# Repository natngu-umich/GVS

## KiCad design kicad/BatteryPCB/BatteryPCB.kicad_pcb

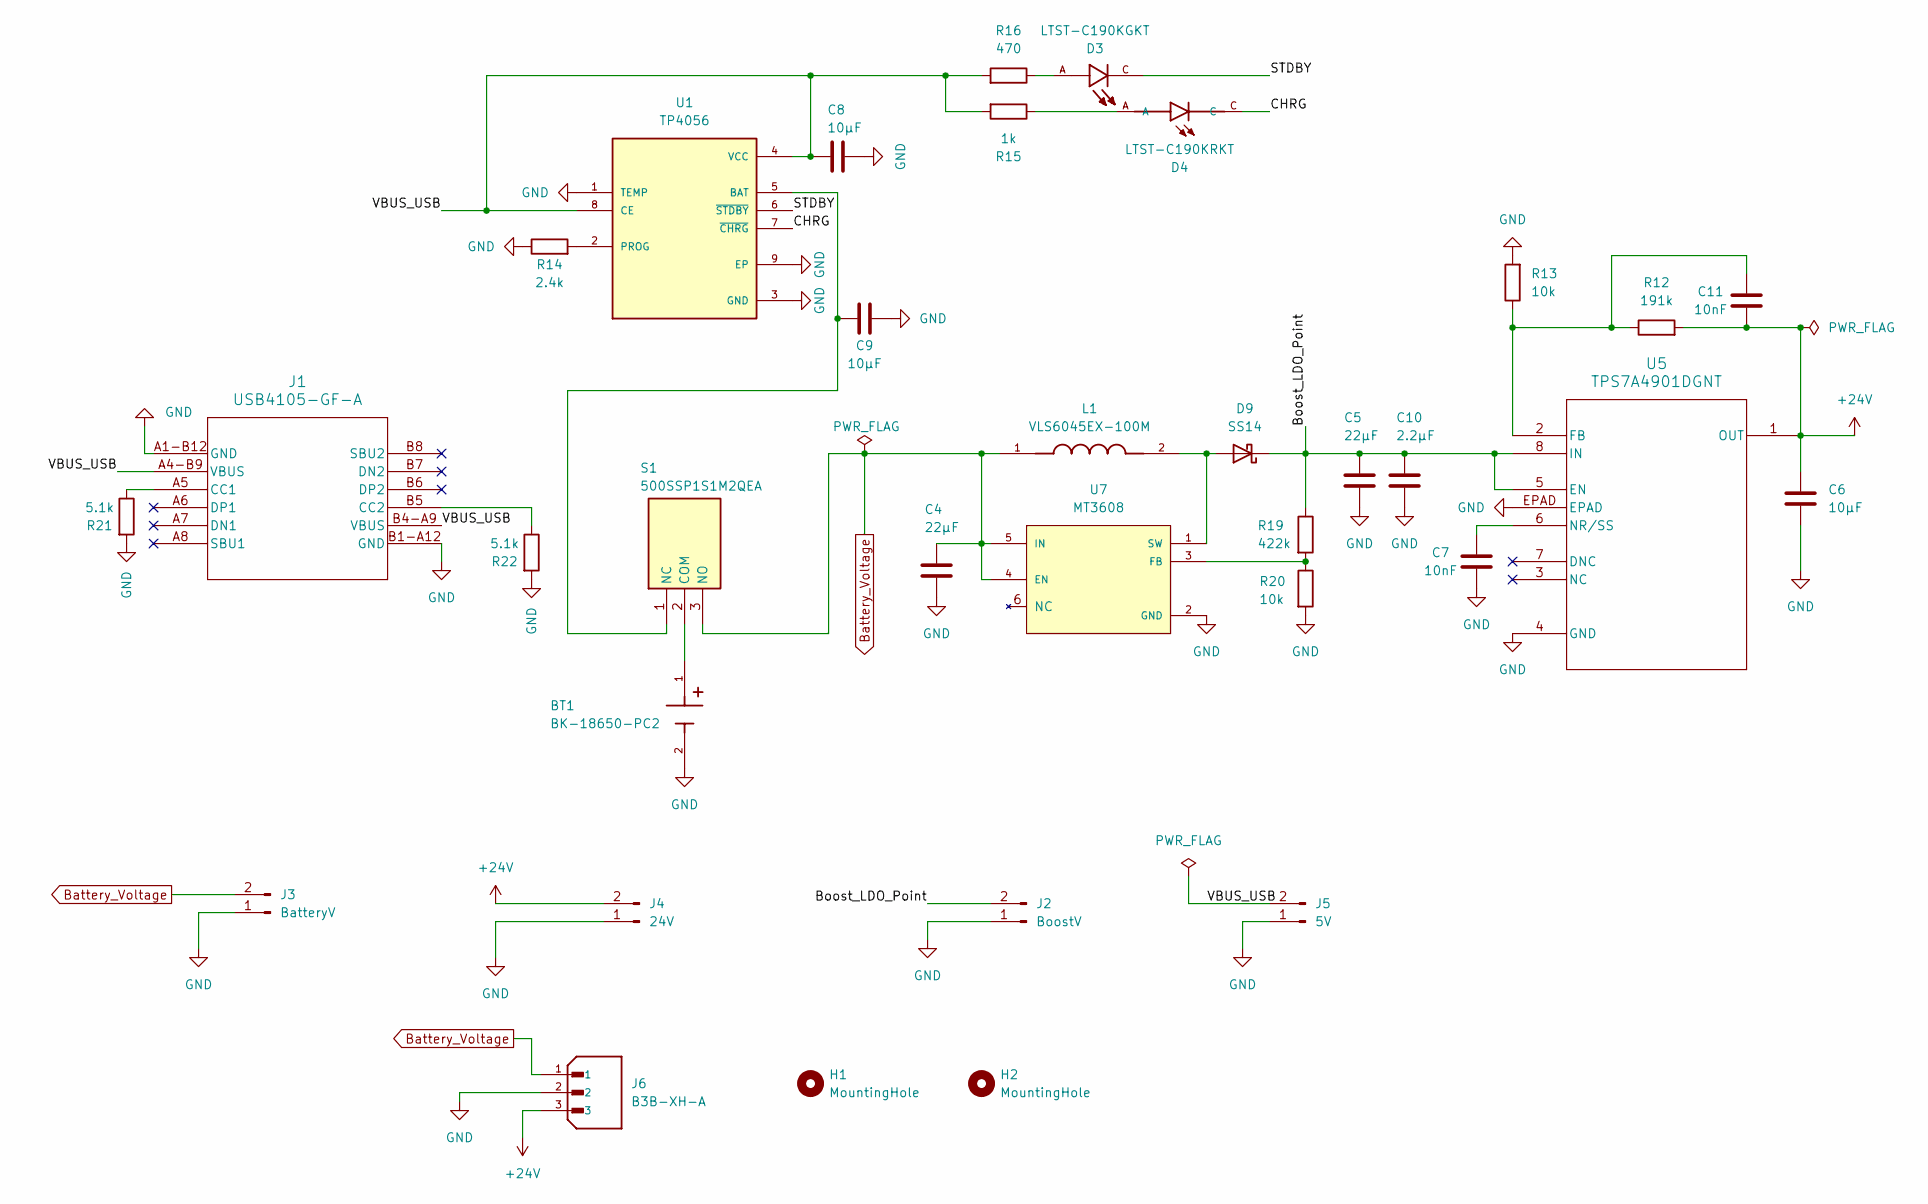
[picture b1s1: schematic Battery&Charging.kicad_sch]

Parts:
BT1: BK-18650-PC2; BH-18650-B1BA002; PARTREV F
C4, C5: 22µF; C_0805_2012Metric_Pad1.18x1.45mm_HandSolder
C6, C8, C9: 10µF; C_0805_2012Metric_Pad1.18x1.45mm_HandSolder
C7, C11: 10nF; C_0805_2012Metric_Pad1.18x1.45mm_HandSolder
C10: 2.2µF; C_0805_2012Metric_Pad1.18x1.45mm_HandSolder
D3: LTST-C190KGKT; LEDC1608X35N
D4: LTST-C190KRKT; LEDC1608X35N
D9: SS14; D_SMA
H1, H2: MountingHole; MountingHole_3.5mm
J1: USB4105-GF-A; USB4105_GCT
J2: BoostV; PinSocket_1x02_P2.54mm_Vertical
J3: BatteryV; PinSocket_1x02_P2.54mm_Vertical
J4: 24V; PinSocket_1x02_P2.54mm_Vertical
J5: 5V; PinSocket_1x02_P2.54mm_Vertical
J6: B3B-XH-A; JST_B3B-XH-A; PARTREV 7/4/21
L1: VLS6045EX-100M; IND_VLS6045EX-100M; PARTREV N/A
R12: 191k; R_0805_2012Metric_Pad1.20x1.40mm_HandSolder
R13, R20: 10k; R_0805_2012Metric_Pad1.20x1.40mm_HandSolder
R14: 2.4k; R_0805_2012Metric_Pad1.20x1.40mm_HandSolder
R15: 1k; R_0805_2012Metric_Pad1.20x1.40mm_HandSolder
R16: 470; R_0805_2012Metric_Pad1.20x1.40mm_HandSolder
R19: 422k; R_0805_2012Metric_Pad1.20x1.40mm_HandSolder
R21, R22: 5.1k; R_0805_2012Metric_Pad1.20x1.40mm_HandSolder
S1: 500SSP1S1M2QEA; Mouser Part Number 612-500-A121
U1: TP4056; SOP127P600X175-9N; M_PART_NUMBER TP4056
U5: TPS7A4901DGNT; DGN8_1P89X1P57
U7: MT3608; SOT95P280X145-6N; PARTREV 1.0

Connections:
+24V: C6.1, C11.2, J4.2, J6.3, R12.2, U5.1 (OUT)
/Battery&Charging/Boost_LDO_Point: C5.1, C10.1, D9.1 (K), J2.2, R19.1, U5.5 (EN), U5.8 (IN)
/Battery&Charging/CHRG: D4.C, U1.7 (~CHRG)
/Battery&Charging/STDBY: D3.C, U1.6 (~STDBY)
/Battery&Charging/VBUS_USB: C8.2, J1.A4-B9 (VBUS), J1.B4-A9 (VBUS), J5.2, R15.2, R16.2, U1.4 (VCC), U1.8 (CE)
Battery_Voltage: C4.1, J3.2, J6.1, L1.1, S1.3 (NO), U7.4 (EN), U7.5 (IN)
GND: BT1.2, C4.2, C5.2, C6.2, C7.2, C8.1, C9.2, C10.2, J1.A1-B12 (GND), J1.B1-A12 (GND), J2.1, J3.1, J4.1, J5.1, J6.2, R13.2, R14.1, R20.2, R21.2, R22.2, U1.1 (TEMP), U1.3 (GND), U1.9 (EP), U5.4 (GND), U5.EPAD, U7.2 (GND)
unnamed: D3.A, R16.1
unnamed: D4.A, R15.1
unnamed: D9.2 (A), L1.2, U7.1 (SW)
unnamed: J1.A5 (CC1), R21.1
unnamed: J1.B5 (CC2), R22.1
unnamed: BT1.1, S1.2 (COM)
unnamed: C9.1, S1.1 (NC), U1.5 (BAT)
unnamed: R14.2, U1.2 (PROG)
unnamed: C11.1, R12.1, R13.1, U5.2 (FB)
unnamed: C7.1, U5.6 (NR/SS)
unnamed: R19.2, R20.1, U7.3 (FB)

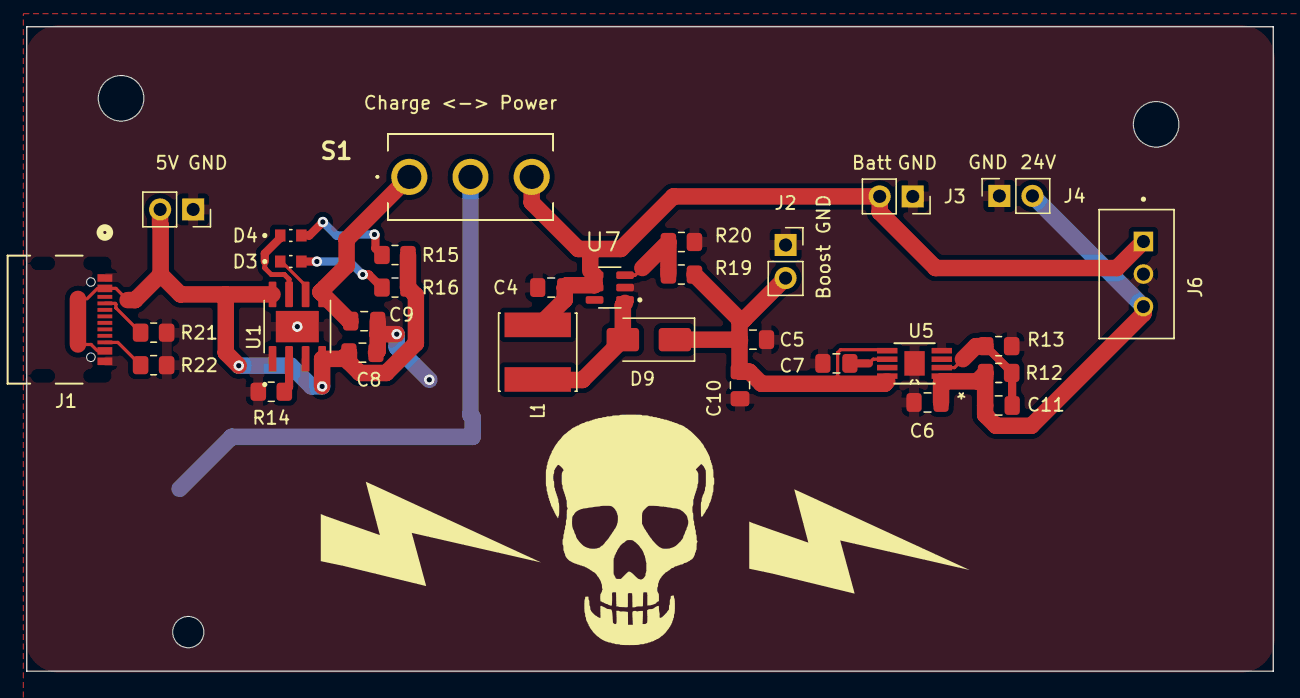
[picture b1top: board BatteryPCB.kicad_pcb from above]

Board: 2 copper layers, 95.8 x 49.5 mm, 34 parts (1 on the bottom side), 18 nets.

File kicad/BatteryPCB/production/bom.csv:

Designator,Footprint,Quantity,Value,LCSC Part #
C10,0805,1,2.2µF,
"C11, C7",0805,2,10nF,
"C4, C5",0805,2,22µF,
"C6, C8, C9",0805,3,10µF,
D3,LEDC1608X35N,1,LTST-C190KGKT,
D4,LEDC1608X35N,1,LTST-C190KRKT,
D9,D_SMA,1,SS14,
J1,USB4105_GCT,1,USB4105-GF-A,
J2,PinSocket_1x02_P2.54mm_Vertical,1,BoostV,
J3,PinSocket_1x02_P2.54mm_Vertical,1,BatteryV,
J4,PinSocket_1x02_P2.54mm_Vertical,1,24V,
J5,PinSocket_1x02_P2.54mm_Vertical,1,5V,
J6,JST_B3B-XH-A,1,B3B-XH-A,
L1,IND_VLS6045EX-100M,1,VLS6045EX-100M,
R12,0805,1,191k,
"R13, R20",0805,2,10k,
R14,0805,1,2.4k,
R15,0805,1,1k,
R16,0805,1,470,
R19,0805,1,422k,
"R21, R22",0805,2,5.1k,
S1,500SSP1S1M2QEA,1,500SSP1S1M2QEA,
U1,SOP127P600X175-9N,1,TP4056,
U5,DGN8_1P89X1P57,1,TPS7A4901DGNT,
U7,SOT95P280X145-6N,1,MT3608,

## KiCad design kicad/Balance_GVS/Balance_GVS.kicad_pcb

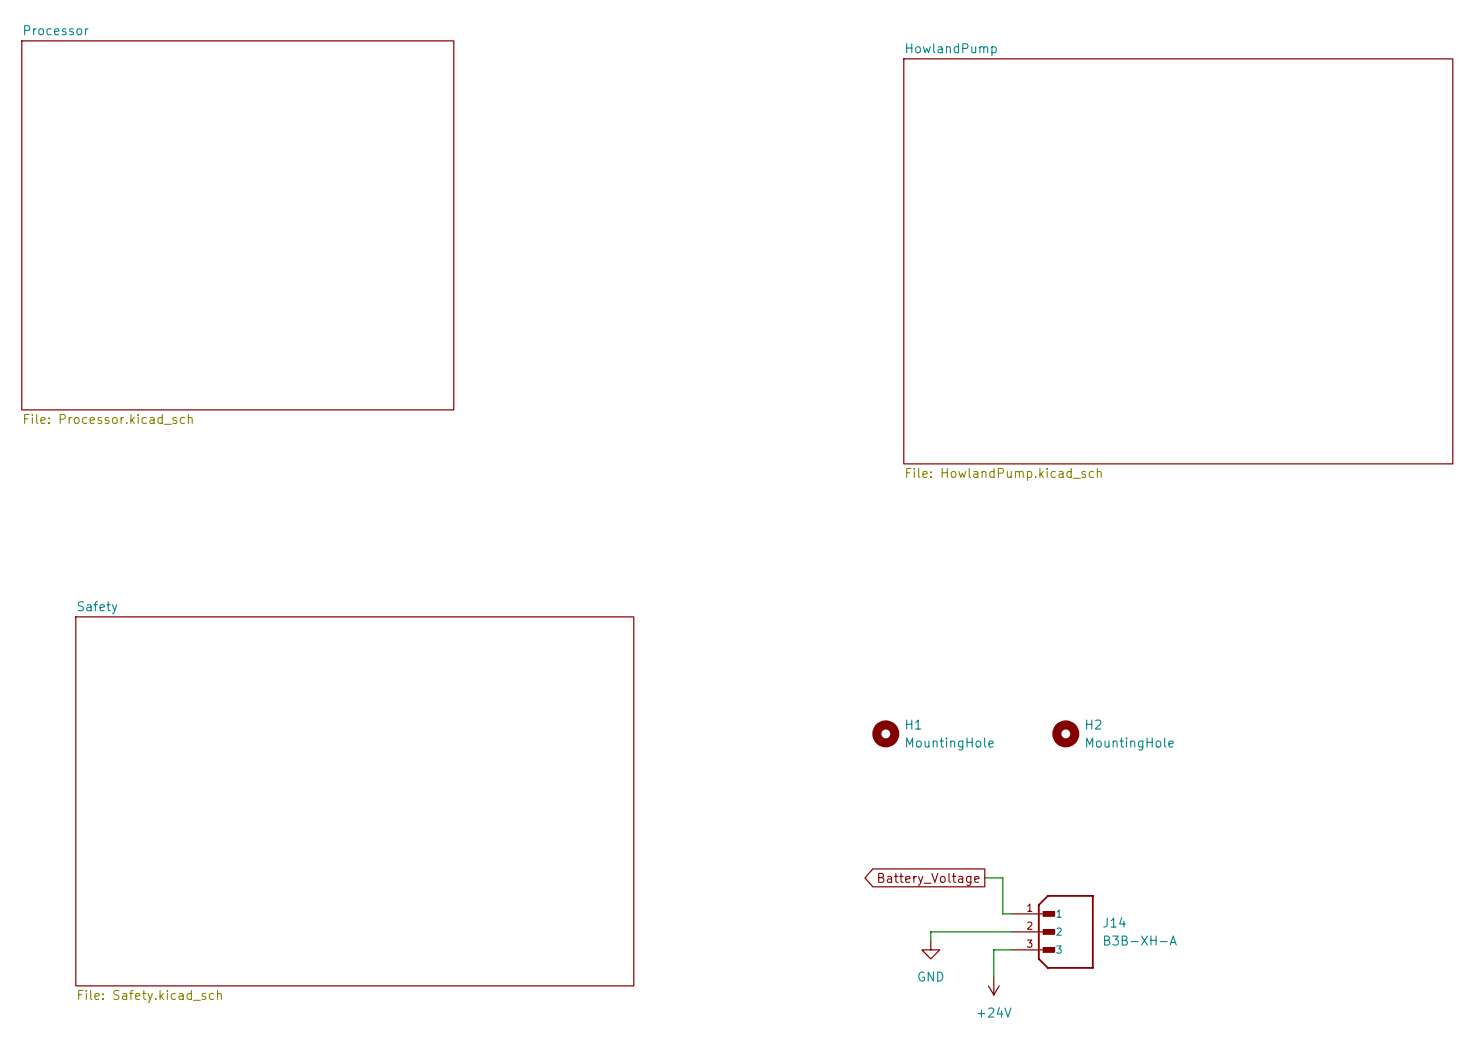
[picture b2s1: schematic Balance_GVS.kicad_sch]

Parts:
H1, H2: MountingHole; MountingHole_3.5mm
J14: B3B-XH-A; JST_B3B-XH-A; PARTREV 7/4/21

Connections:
+24V: J14.3; also elsewhere on the board
Battery_Voltage: J14.1; also elsewhere on the board
GND: J14.2; also elsewhere on the board

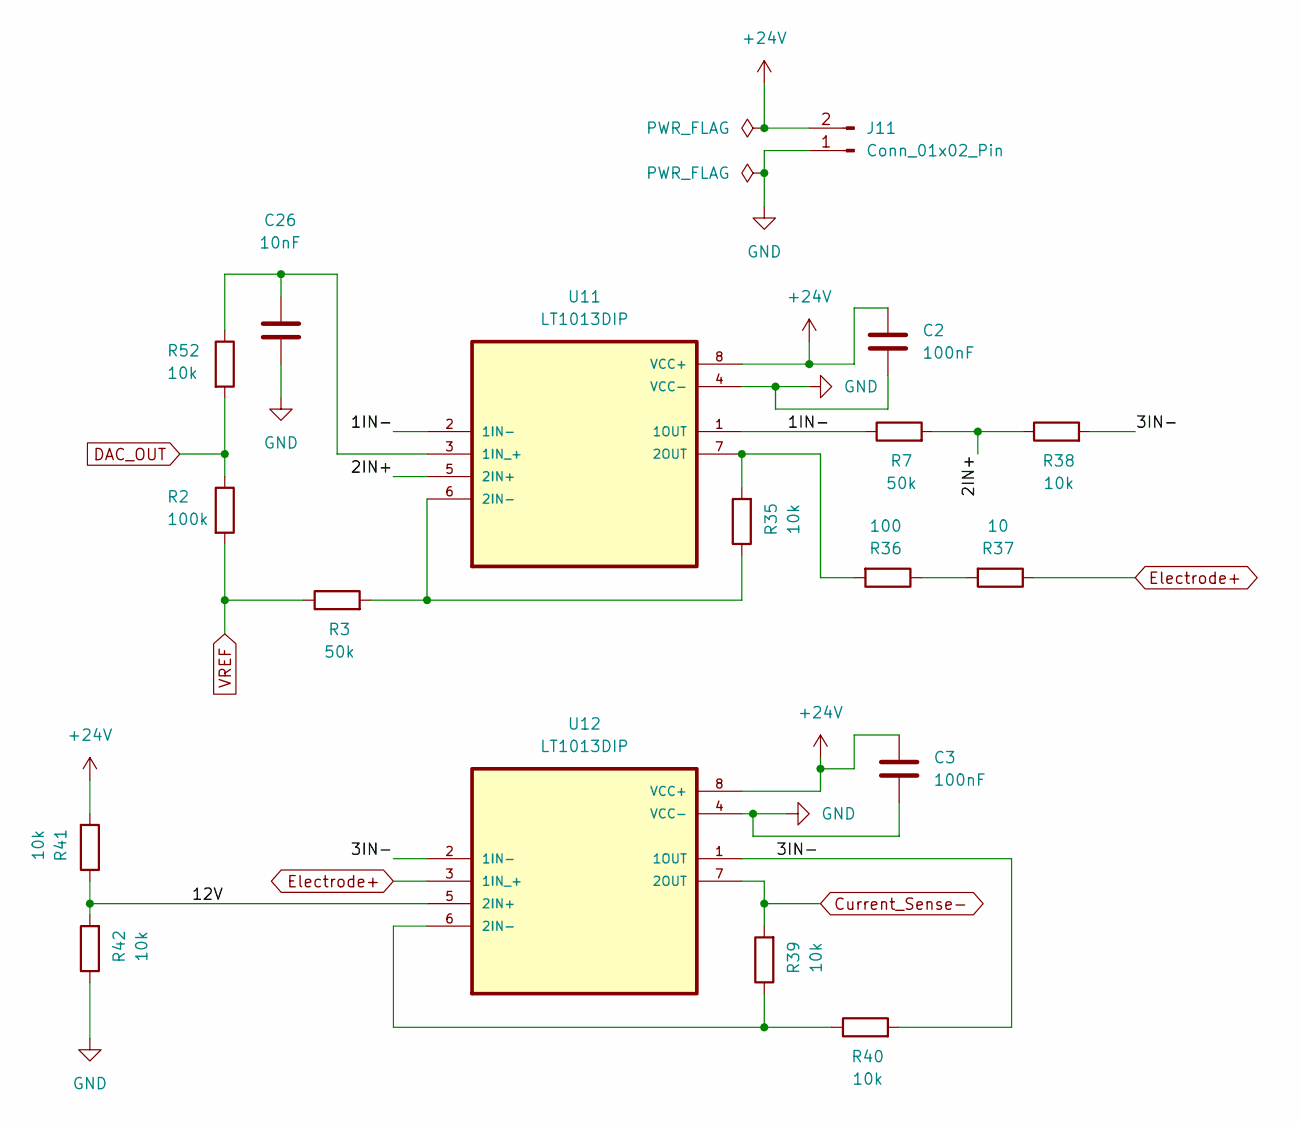
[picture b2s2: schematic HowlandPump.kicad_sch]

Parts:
C2, C3: 100nF; C_0805_2012Metric_Pad1.18x1.45mm_HandSolder
C26: 10nF; C_0805_2012Metric_Pad1.18x1.45mm_HandSolder
J11: Conn_01x02_Pin; PinSocket_1x02_P2.54mm_Vertical
R2: 100k; R_0805_2012Metric_Pad1.20x1.40mm_HandSolder
R3, R7: 50k; R_0805_2012Metric_Pad1.20x1.40mm_HandSolder
R35, R38, R39, R40, R41, R42, R52: 10k; R_0805_2012Metric_Pad1.20x1.40mm_HandSolder
R36: 100; R_0805_2012Metric_Pad1.20x1.40mm_HandSolder
R37: 10; R_0805_2012Metric_Pad1.20x1.40mm_HandSolder
U11, U12: LT1013DIP; DIP794W45P254L959H508Q8; DigiKey_Part_Number 296-7044-5-ND

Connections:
+24V: C2.1, C3.1, J11.2, R41.2, U11.8 (VCC+), U12.8 (VCC+); also elsewhere on the board
/HowlandPump/1IN-: R7.1, U11.1 (1OUT), U11.2 (1IN-)
/HowlandPump/2IN+: R7.2, R38.1, U11.5 (2IN+)
/HowlandPump/3IN-: R38.2, R40.2, U12.1 (1OUT), U12.2 (1IN-)
/HowlandPump/12V: R41.1, R42.2, U12.5 (2IN+)
Current_Sense-: R39.2, U12.7 (2OUT); also elsewhere on the board
DAC_OUT: R2.1, R52.2; also elsewhere on the board
Electrode+: R37.1, U12.3 (1IN_+); also elsewhere on the board
GND: C2.2, C3.2, C26.2, J11.1, R42.1, U11.4 (VCC-), U12.4 (VCC-); also elsewhere on the board
unnamed: R36.1, R37.2
unnamed: C26.1, R52.1, U11.3 (1IN_+)
unnamed: R3.2, R35.1, U11.6 (2IN-)
unnamed: R35.2, R36.2, U11.7 (2OUT)
unnamed: R39.1, R40.1, U12.6 (2IN-)
VREF: R2.2, R3.1; also elsewhere on the board

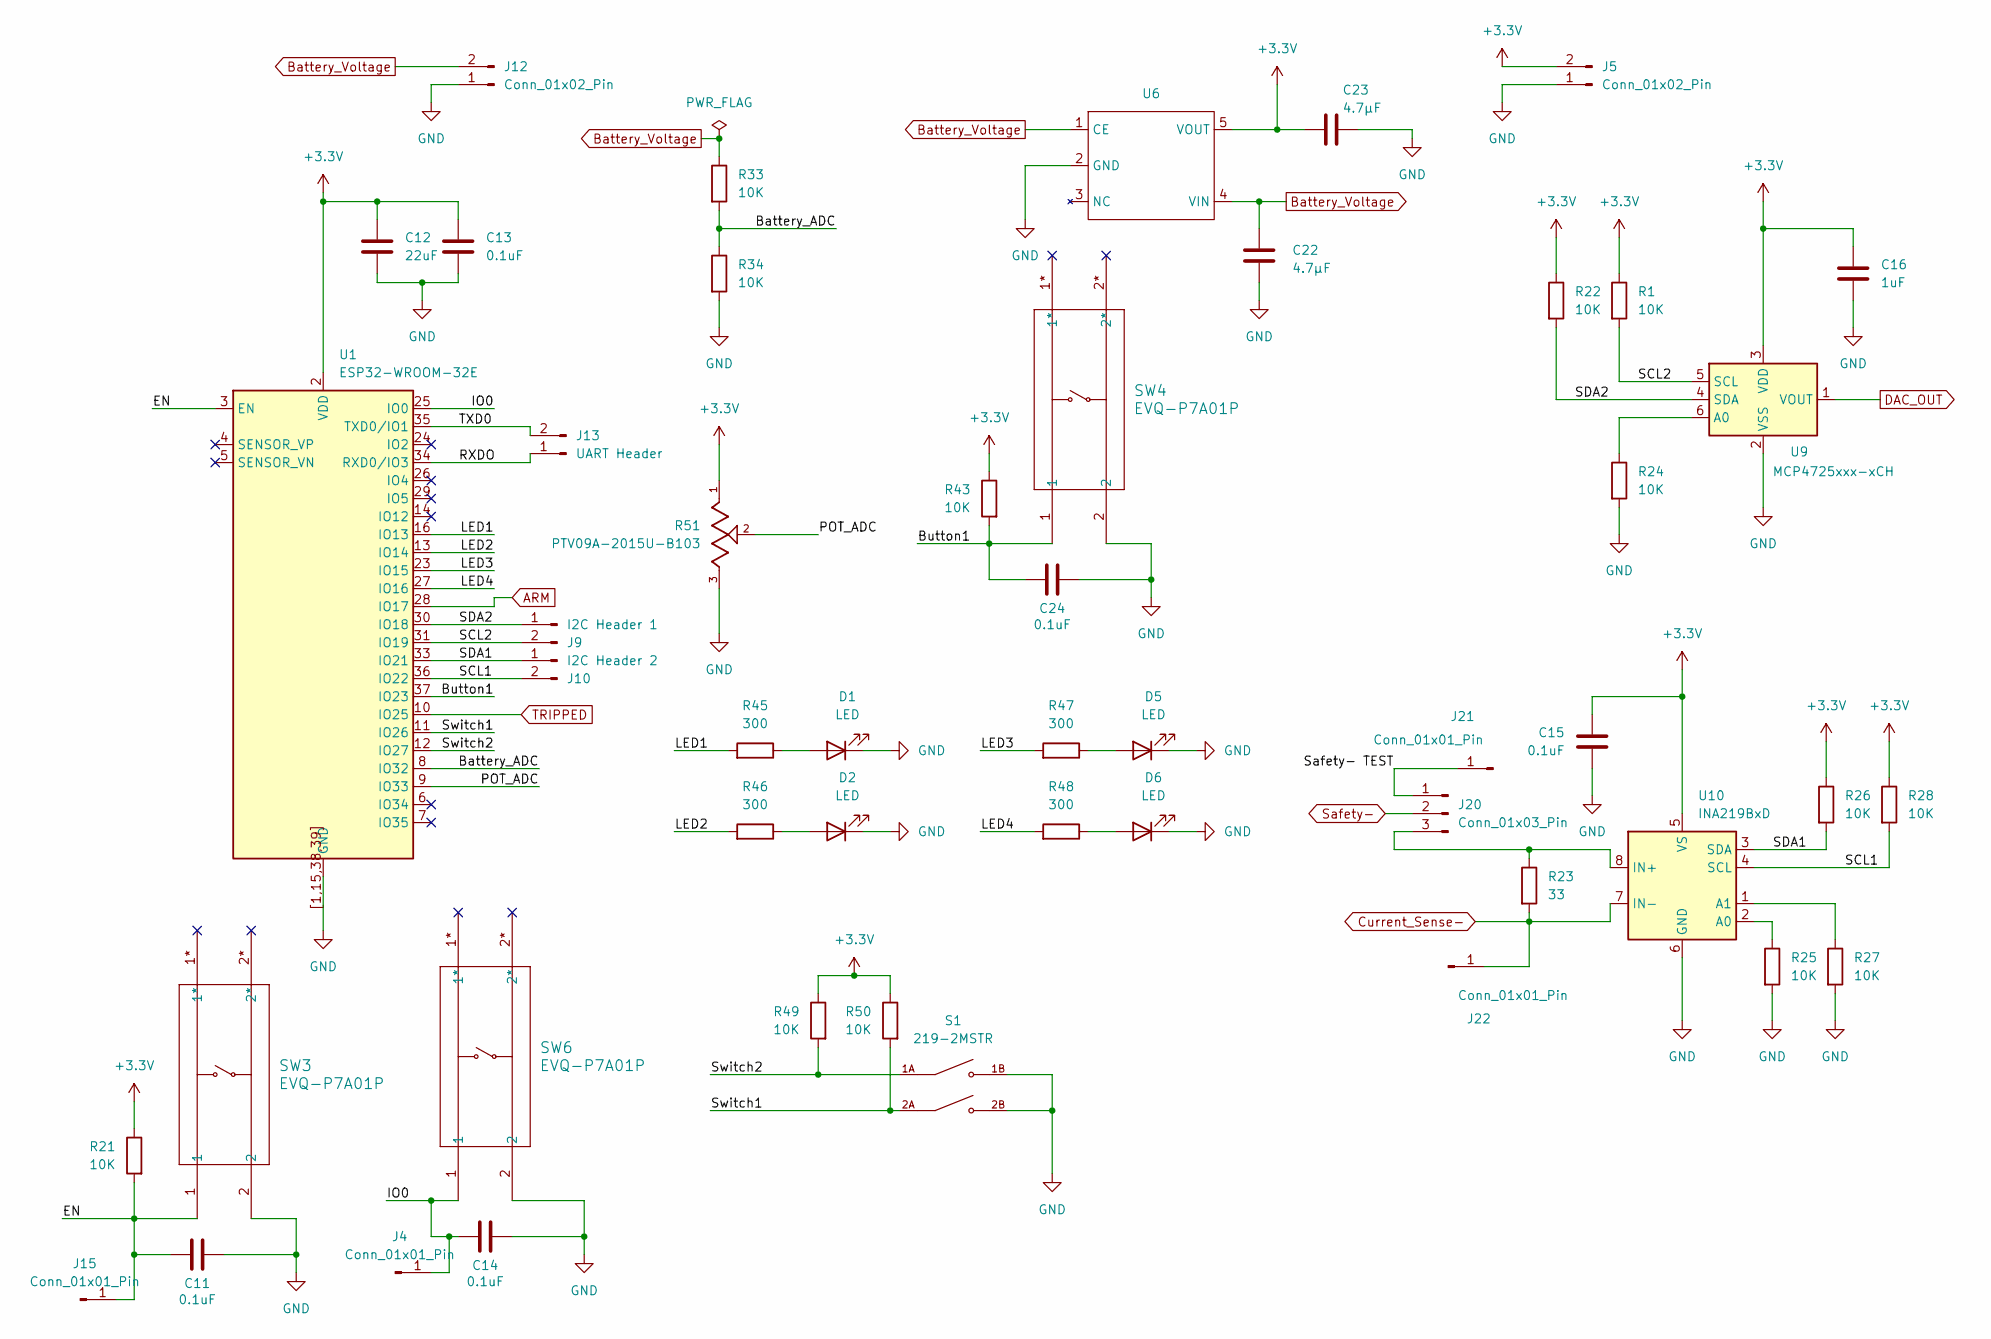
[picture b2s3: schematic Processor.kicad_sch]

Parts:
C11, C13, C14, C15, C24: 0.1uF; C_0805_2012Metric_Pad1.18x1.45mm_HandSolder
C12: 22uF; C_0805_2012Metric_Pad1.18x1.45mm_HandSolder
C16: 1uF; C_0805_2012Metric_Pad1.18x1.45mm_HandSolder
C22, C23: 4.7µF; C_0805_2012Metric_Pad1.18x1.45mm_HandSolder
D1, D2, D5, D6: LED; LED_0603_1608Metric_Pad1.05x0.95mm_HandSolder
J4, J15, J21, J22: Conn_01x01_Pin; PinSocket_1x01_P2.54mm_Vertical
J5, J12: Conn_01x02_Pin; PinSocket_1x02_P2.54mm_Vertical
J9: I2C Header 1; PinSocket_1x02_P2.54mm_Vertical
J10: I2C Header 2; PinSocket_1x02_P2.54mm_Vertical
J13: UART Header; PinSocket_1x02_P2.54mm_Vertical
J20: Conn_01x03_Pin; PinHeader_1x03_P2.54mm_Vertical
R1, R21, R22, R24, R25, R26, R27, R28, R33, R34, R43, R49, R50: 10K; R_0805_2012Metric_Pad1.20x1.40mm_HandSolder
R23: 33; R_0805_2012Metric_Pad1.20x1.40mm_HandSolder
R45, R46, R47, R48: 300; R_0805_2012Metric_Pad1.20x1.40mm_HandSolder
R51: PTV09A-2015U-B103; TRIM_PTV09A-2015U-B103; PARTREV 01/20
S1: 219-2MSTR; SW_219-2MSTR; PARTREV B
SW3, SW4, SW6: EVQ-P7A01P; EVQ_P7_PAN
U1: ESP32-WROOM-32E
U6: SOT-89-5_Handsoldering
U9: MCP4725xxx-xCH; SOT-23-6
U10: INA219BxD; SOIC-8_3.9x4.9mm_P1.27mm

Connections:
+3.3V: C12.1, C13.1, C15.1, C16.1, C23.2, J5.2, R1.1, R21.1, R22.1, R26.1, R28.1, R43.1, R49.1, R50.1, R51.1, U1.2 (VDD), U6.5 (VOUT), U9.3 (VDD), U10.5 (VS); also elsewhere on the board
/Processor/Battery_ADC: R33.2, R34.1, U1.8 (IO32)
/Processor/Button1: C24.1, R43.2, SW4.1, U1.37 (IO23)
/Processor/EN: C11.1, J15.1 (Pin_1_1), R21.2, SW3.1, U1.3 (EN)
/Processor/IO0: C14.1, J4.1 (Pin_1_1), SW6.1, U1.25 (IO0)
/Processor/LED1: R45.2, U1.16 (IO13)
/Processor/LED2: R46.2, U1.13 (IO14)
/Processor/LED3: R47.2, U1.23 (IO15)
/Processor/LED4: R48.2, U1.27 (IO16)
/Processor/POT_ADC: R51.2, U1.9 (IO33)
/Processor/RXDO: J13.1, U1.34 (RXD0/IO3)
/Processor/SCL1: J10.2, R28.2, U1.36 (IO22), U10.4 (SCL)
/Processor/SCL2: J9.2, R1.2, U1.31 (IO19), U9.5 (SCL)
/Processor/SDA1: J10.1, R26.2, U1.33 (IO21), U10.3 (SDA)
/Processor/SDA2: J9.1, R22.2, U1.30 (IO18), U9.4 (SDA)
/Processor/Safety- TEST: J20.1, J21.1 (Pin_1_1)
/Processor/Switch1: R50.2, S1.2A, U1.11 (IO26)
/Processor/Switch2: R49.2, S1.1A, U1.12 (IO27)
/Processor/TXD0: J13.2, U1.35 (TXD0/IO1)
ARM: U1.28 (IO17); also elsewhere on the board
Battery_Voltage: C22.1, J12.2, R33.1, U6.1 (CE), U6.4 (VIN); also elsewhere on the board
Current_Sense-: J22.1 (Pin_1_1), R23.2, U10.7 (IN-); also elsewhere on the board
DAC_OUT: U9.1 (VOUT); also elsewhere on the board
GND: C11.2, C12.2, C13.2, C14.2, C15.2, C16.2, C22.2, C23.1, C24.2, D1.1 (K), D2.1 (K), D5.1 (K), D6.1 (K), J5.1, J12.1, R24.2, R25.2, R27.2, R34.2, R51.3, S1.1B, S1.2B, SW3.2, SW4.2, SW6.2, U1.1 (GND), U1.15 (GND), U1.38 (GND), U1.39 (GND), U1.[1,15,38,39] (GND), U6.2 (GND), U9.2 (VSS), U10.6 (GND); also elsewhere on the board
unnamed: D1.2 (A), R45.1
unnamed: D2.2 (A), R46.1
unnamed: D5.2 (A), R47.1
unnamed: D6.2 (A), R48.1
unnamed: J20.3, R23.1, U10.8 (IN+)
unnamed: R24.1, U9.6 (A0)
unnamed: R25.1, U10.2 (A0)
unnamed: R27.1, U10.1 (A1)
Safety-: J20.2; also elsewhere on the board
TRIPPED: U1.10 (IO25); also elsewhere on the board

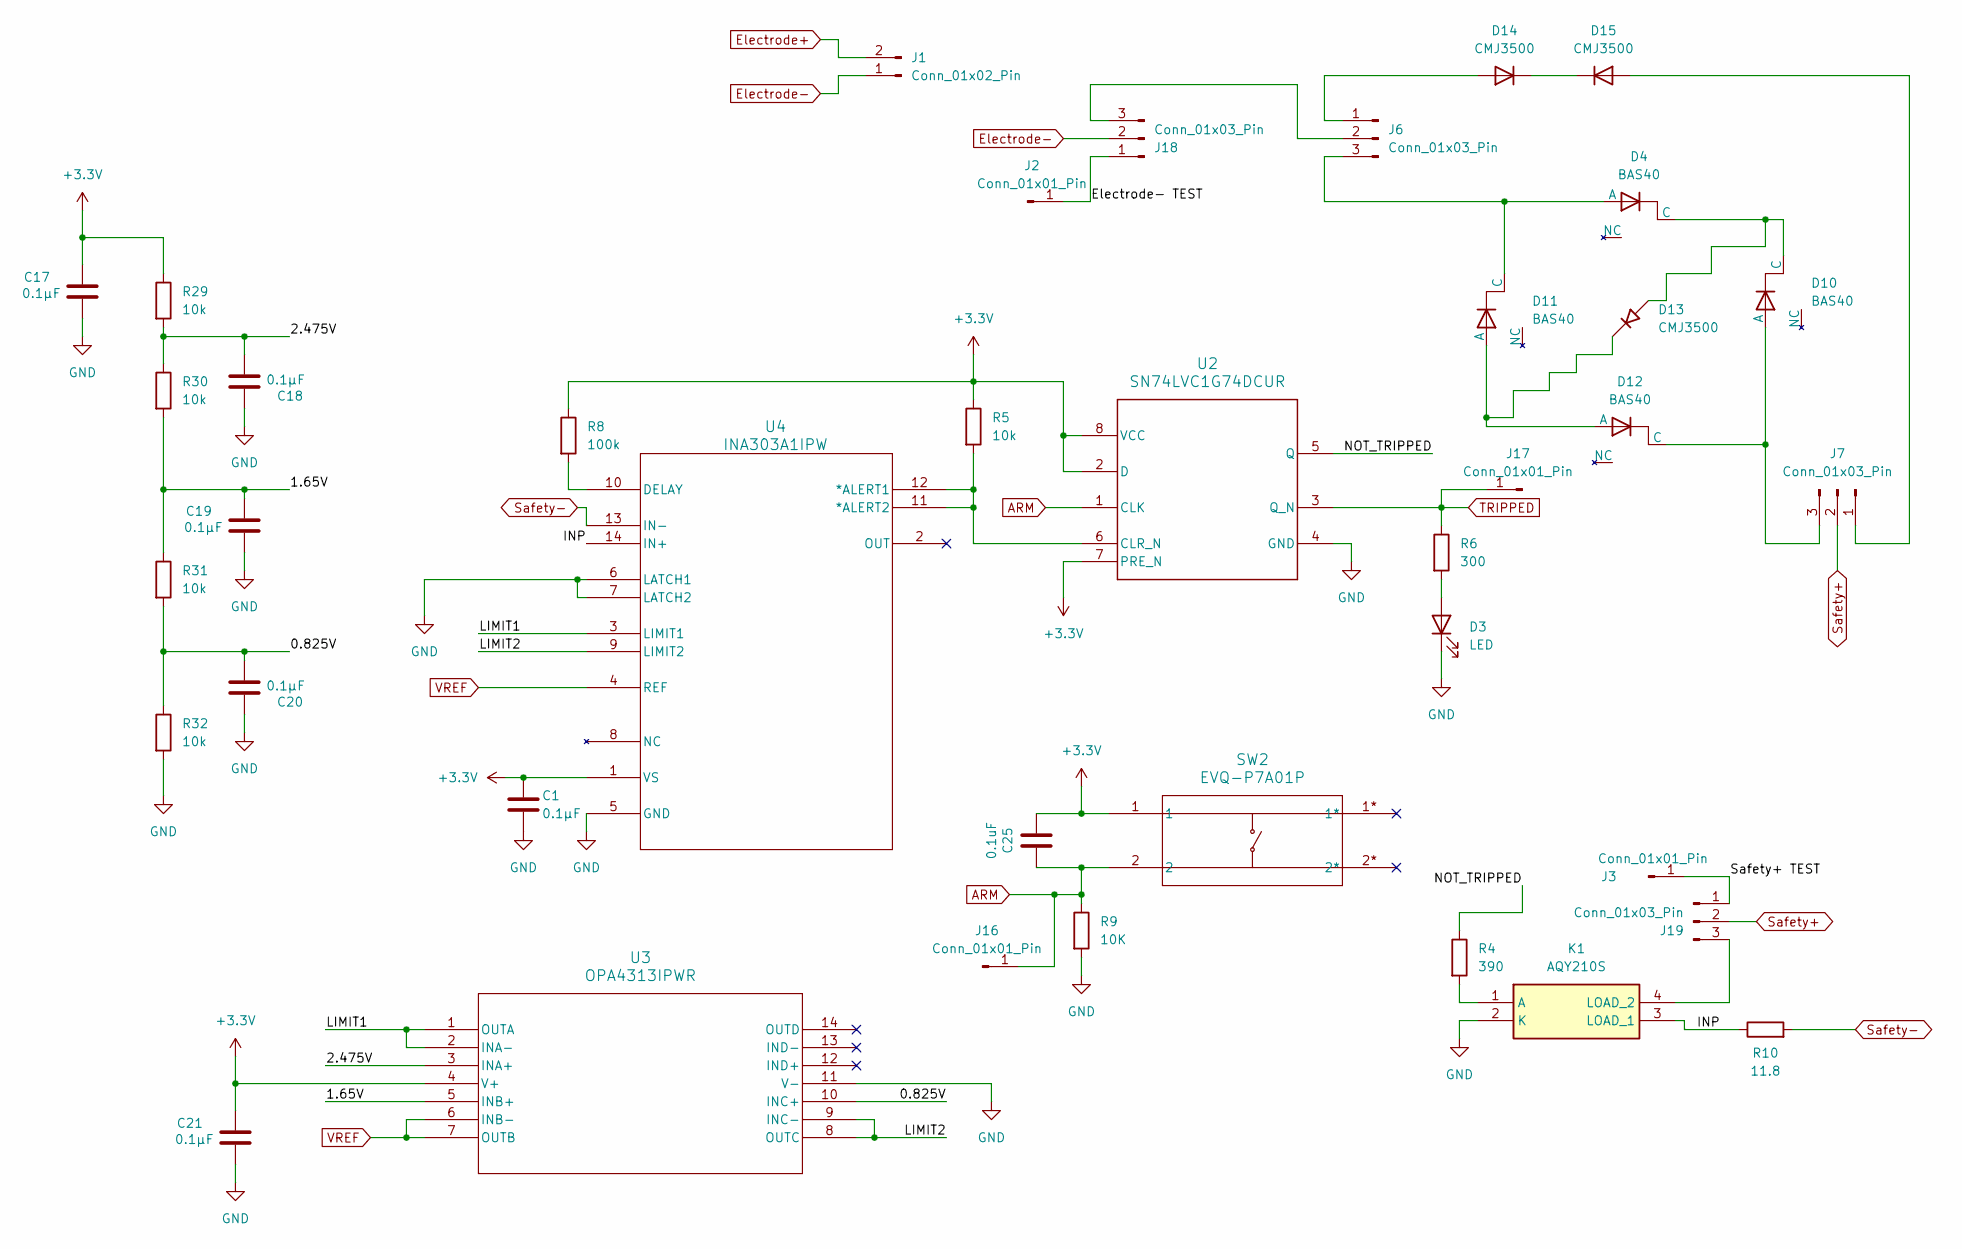
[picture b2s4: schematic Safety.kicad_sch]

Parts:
C1, C17, C18, C19, C20, C21: 0.1µF; C_0805_2012Metric_Pad1.18x1.45mm_HandSolder
C25: 0.1uF; C_0805_2012Metric_Pad1.18x1.45mm_HandSolder
D3: LED; LED_0603_1608Metric_Pad1.05x0.95mm_HandSolder
D4, D10, D11, D12: BAS40; P200_SOT-23
D13, D14, D15: CMJ3500; D_SOD-123F
J1: Conn_01x02_Pin; PinSocket_1x02_P2.54mm_Vertical
J2, J3, J16, J17: Conn_01x01_Pin; PinSocket_1x01_P2.54mm_Vertical
J6, J7, J18, J19: Conn_01x03_Pin; PinHeader_1x03_P2.54mm_Vertical
K1: AQY210S; SOP254P962X275-4N; Mouser Part Number 769-AQY210S
R4: 390; R_0805_2012Metric_Pad1.20x1.40mm_HandSolder
R5, R29, R30, R31, R32: 10k; R_0805_2012Metric_Pad1.20x1.40mm_HandSolder
R6: 300; R_0805_2012Metric_Pad1.20x1.40mm_HandSolder
R8: 100k; R_0805_2012Metric_Pad1.20x1.40mm_HandSolder
R9: 10K; R_0805_2012Metric_Pad1.20x1.40mm_HandSolder
R10: 11.8; R_0805_2012Metric_Pad1.20x1.40mm_HandSolder
SW2: EVQ-P7A01P; EVQ_P7_PAN
U2: SN74LVC1G74DCUR; DCU0008A_M
U3: OPA4313IPWR; PW14_TEX
U4: INA303A1IPW; PW14_TEX

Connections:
+3.3V: C1.2, C17.1, C21.1, C25.1, R5.1, R8.1, R29.1, SW2.1, U2.2 (D), U2.7 (PRE_N), U2.8 (VCC), U3.4 (V+), U4.1 (VS); also elsewhere on the board
/Safety/0.825V: C20.2, R31.2, R32.1, U3.10 (INC+)
/Safety/1.65V: C19.1, R30.2, R31.1, U3.5 (INB+)
/Safety/2.475V: C18.2, R29.2, R30.1, U3.3 (INA+)
/Safety/Electrode- TEST: J2.1 (Pin_1_1), J18.1
/Safety/INP: K1.3 (LOAD_1), R10.1, U4.14 (IN+)
/Safety/LIMIT1: U3.1 (OUTA), U3.2 (INA-), U4.3 (LIMIT1)
/Safety/LIMIT2: U3.8 (OUTC), U3.9 (INC-), U4.9 (LIMIT2)
/Safety/NOT_TRIPPED: R4.1, U2.5 (Q)
/Safety/Safety+ TEST: J3.1 (Pin_1_1), J19.1
ARM: C25.2, J16.1 (Pin_1_1), R9.1, SW2.2, U2.1 (CLK); also elsewhere on the board
Electrode+: J1.2; also elsewhere on the board
Electrode-: J1.1, J18.2
GND: C1.1, C17.2, C18.1, C19.2, C20.1, C21.2, D3.1 (K), K1.2 (K), R9.2, R32.2, U2.4 (GND), U3.11 (V-), U4.5 (GND), U4.6 (LATCH1), U4.7 (LATCH2); also elsewhere on the board
unnamed: D3.2 (A), R6.2
unnamed: D10.1 (A), D12.2 (C), J7.3
unnamed: D4.2 (C), D10.2 (C), D13.2 (A)
unnamed: D11.1 (A), D12.1 (A), D13.1 (K)
unnamed: D4.1 (A), D11.2 (C), J6.3
unnamed: D14.2 (A), J6.1
unnamed: D14.1 (K), D15.1 (K)
unnamed: D15.2 (A), J7.1
unnamed: J6.2, J18.3
unnamed: J19.3, K1.4 (LOAD_2)
unnamed: K1.1 (A), R4.2
unnamed: R5.2, U2.6 (CLR_N), U4.11 (*ALERT2), U4.12 (*ALERT1)
unnamed: R8.2, U4.10 (DELAY)
Safety+: J7.2, J19.2
Safety-: R10.2, U4.13 (IN-); also elsewhere on the board
TRIPPED: J17.1 (Pin_1_1), R6.1, U2.3 (Q_N); also elsewhere on the board
VREF: U3.6 (INB-), U3.7 (OUTB), U4.4 (REF); also elsewhere on the board

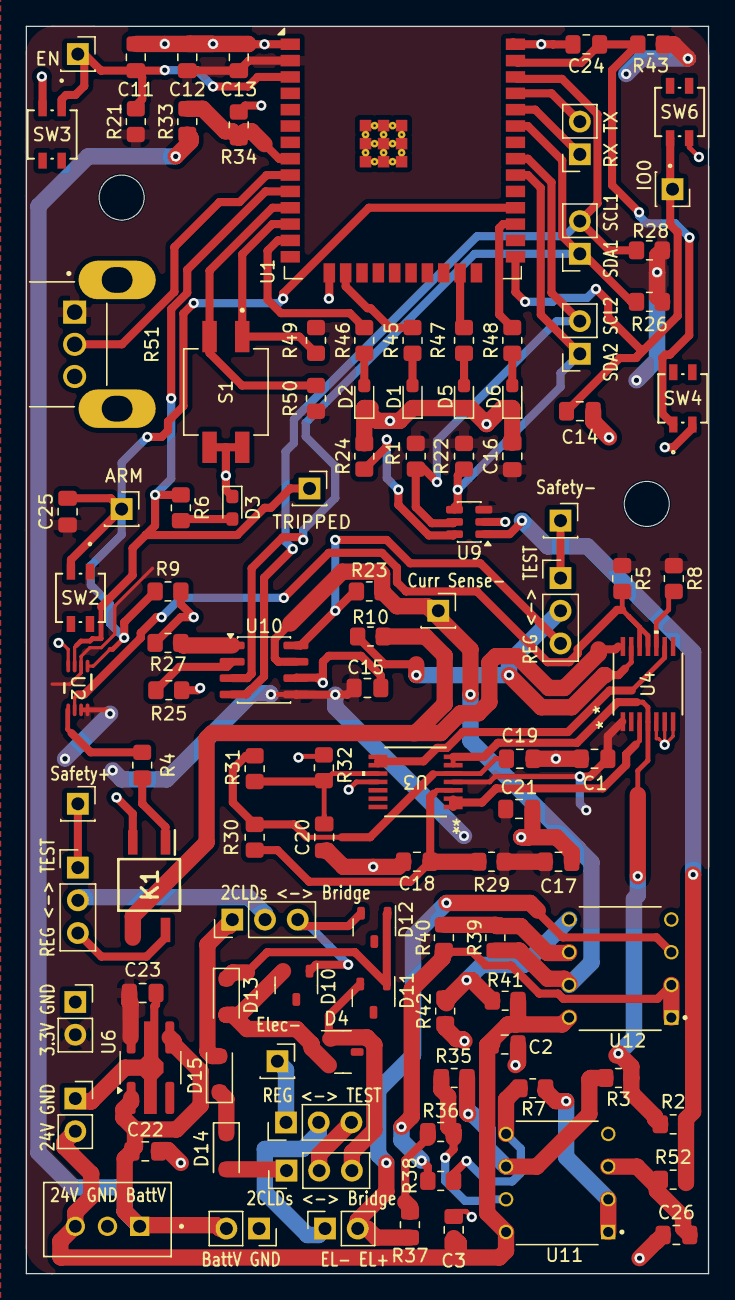
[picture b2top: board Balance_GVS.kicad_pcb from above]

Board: 2 copper layers, 53.0 x 96.9 mm, 110 parts (0 on the bottom side), 70 nets.

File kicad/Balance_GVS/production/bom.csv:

Designator,Footprint,Quantity,Value,LCSC Part #
"C1, C17, C18, C19, C20, C21",0805,6,0.1µF,
"C11, C13, C14, C15, C24, C25",0805,6,0.1uF,
C12,0805,1,22uF,
C16,0805,1,1uF,
"C2, C3",0805,2,100nF,
"C22, C23",0805,2,4.7µF,
C26,0805,1,10nF,
"D1, D2, D3, D5, D6",0603,5,LED,
"D10, D11, D12, D4",P200_SOT-23,4,BAS40,
"D13, D14, D15",D_SOD-123F,3,CMJ3500,
"J1, J11, J12, J5",PinSocket_1x02_P2.54mm_Vertical,4,Conn_01x02_Pin,
J10,PinSocket_1x02_P2.54mm_Vertical,1,I2C Header 2,
J13,PinSocket_1x02_P2.54mm_Vertical,1,UART Header,
J14,JST_B3B-XH-A,1,B3B-XH-A,
"J15, J16, J17, J2, J21, J22, J3, J4",PinSocket_1x01_P2.54mm_Vertical,8,Conn_01x01_Pin,
"J18, J19, J20, J6, J7",PinHeader_1x03_P2.54mm_Vertical,5,Conn_01x03_Pin,
J9,PinSocket_1x02_P2.54mm_Vertical,1,I2C Header 1,
K1,SOP254P962X275-4N,1,AQY210S,
"R1, R21, R22, R24, R25, R26, R27, R28, R29, R30, R31, R32, R33, R34, R35, R38, R39, R40, R41, R42, R43, R49, R5, R50, R52, R9",0805,26,10K,
R10,0805,1,11.8,
"R2, R8",0805,2,100k,
R23,0805,1,33,
"R3, R7",0805,2,50k,
R36,0805,1,100,
R37,0805,1,10,
R4,0805,1,390,
"R45, R46, R47, R48, R6",0805,5,300,
R51,TRIM_PTV09A-2015U-B103,1,PTV09A-2015U-B103,
S1,SW_219-2MSTR,1,219-2MSTR,
"SW2, SW3, SW4, SW6",EVQ_P7_PAN,4,EVQ-P7A01P,
U1,ESP32-WROOM-32E,1,ESP32-WROOM-32E,
U10,SOIC-8_3.9x4.9mm_P1.27mm,1,INA219BxD,
"U11, U12",DIP794W45P254L959H508Q8,2,LT1013DIP,
U2,DCU0008A_M,1,SN74LVC1G74DCUR,
U3,PW14_TEX,1,OPA4313IPWR,
U4,PW14_TEX,1,INA303A1IPW,
U6,SOT-89-5_Handsoldering,1,~,
U9,SOT-23-6,1,MCP4725xxx-xCH,
